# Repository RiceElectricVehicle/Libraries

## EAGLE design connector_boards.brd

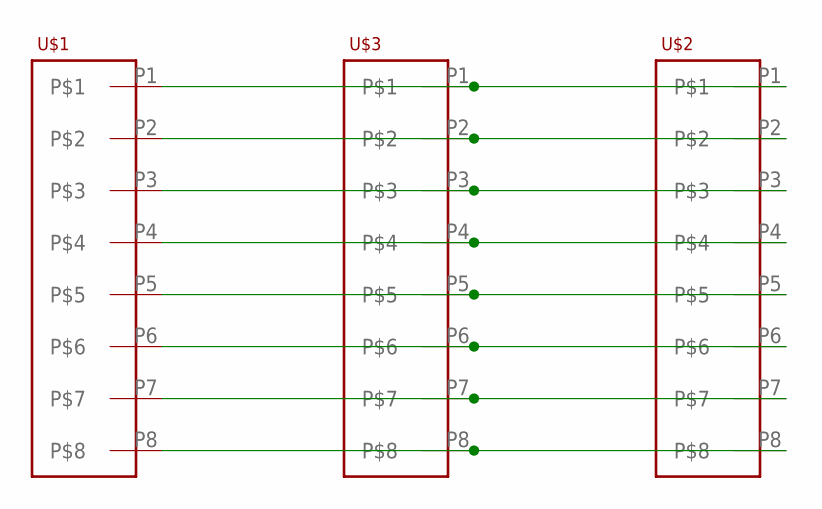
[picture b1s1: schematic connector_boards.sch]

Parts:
U$1, U$2, U$3: 8-PIN-MOLEX-RA-FEMALE; 8-PIN-MOLEX

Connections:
unnamed: U$1.P1, U$2.P1, U$3.P1
unnamed: U$1.P2, U$2.P2, U$3.P2
unnamed: U$1.P3, U$2.P3, U$3.P3
unnamed: U$1.P4, U$2.P4, U$3.P4
unnamed: U$1.P5, U$2.P5, U$3.P5
unnamed: U$1.P6, U$2.P6, U$3.P6
unnamed: U$1.P7, U$2.P7, U$3.P7
unnamed: U$1.P8, U$2.P8, U$3.P8

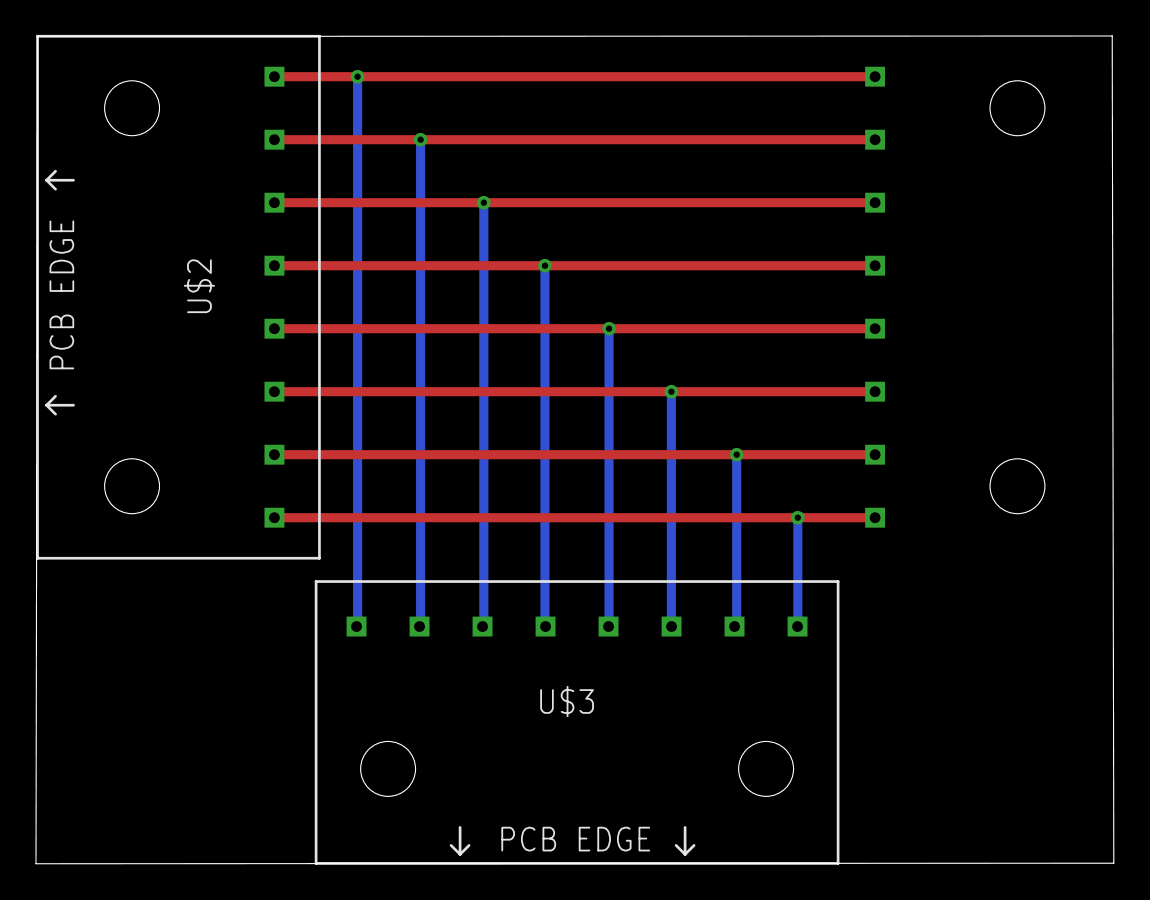
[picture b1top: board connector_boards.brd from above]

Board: 2 copper layers, 59.9 x 46.0 mm, 3 parts (1 on the bottom side), 8 nets.

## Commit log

2018-10-22 Master Library built including most major components!
2018-10-22 some update from aux circuit
2018-11-03 Connector boards
2018-11-15 Return to the original state after major disruption
2018-11-15 My initials added :)
2018-11-15 Starting added attributes to molex connector part (not done)
2018-11-17 messin around with attributes on Molex 8-pin
2018-11-29 Updated parts for ESD (blocks)
2018-12-02 Fixed hole size for 8-pin molex
2018-12-02 New connector added, changed trace width, drill size and via diameter
2019-01-07 Fixed L6390 package
2019-01-08 fixes new L6390 package with correct footprints
2019-02-01 small change to 8-pin molex
2019-02-05 Adds new murata buck and test loop
2019-02-06 Adds JST-5pin automotive header
2019-02-06 MAkes 8-pin symbol smaller
2019-02-19 hella changes
2019-02-26 latest changes
